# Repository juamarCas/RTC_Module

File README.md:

# RTC_Module
RTC módule based on the ECS-RTC-3225-5699C3-TR chip

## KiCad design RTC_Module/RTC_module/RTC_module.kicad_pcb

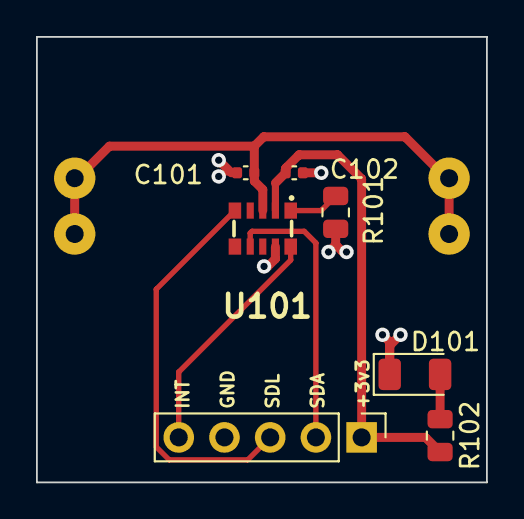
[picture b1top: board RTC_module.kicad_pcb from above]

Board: 2 copper layers, 25.0 x 24.8 mm, 8 parts (1 on the bottom side), 8 nets.

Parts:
C101, C102: 100nF; C_0402_1005Metric
D101: LED_Small; LED_1206_3216Metric
J101: Conn_01x05; PinHeader_1x05_P2.54mm_Vertical
R101: 10k; R_0805_2012Metric
R102: 2k2; R_0805_2012Metric
U101: ECS-RTC-3225-5699C3-TR; ECSRTC32255699C3TR
U102: BAT-HLD-001-THM; BATHLD001THM

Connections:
+3.3V: C102.1, J101.1, R102.2, U101.2 (VDD)
/INT: J101.5, U101.10 (~INT)
/SDA: J101.2, U101.7 (SDA)
/SDL: J101.3, U101.5 (SCL)
GND: C101.2, C102.2, D101.1 (K), J101.4, R101.2, U101.9 (GND), U102.5
unnamed: D101.2 (A), R102.1
unnamed: R101.1, U101.1 (FOE)
VDC: C101.1, U101.3 (VBAT), U102.1, U102.2, U102.3, U102.4
